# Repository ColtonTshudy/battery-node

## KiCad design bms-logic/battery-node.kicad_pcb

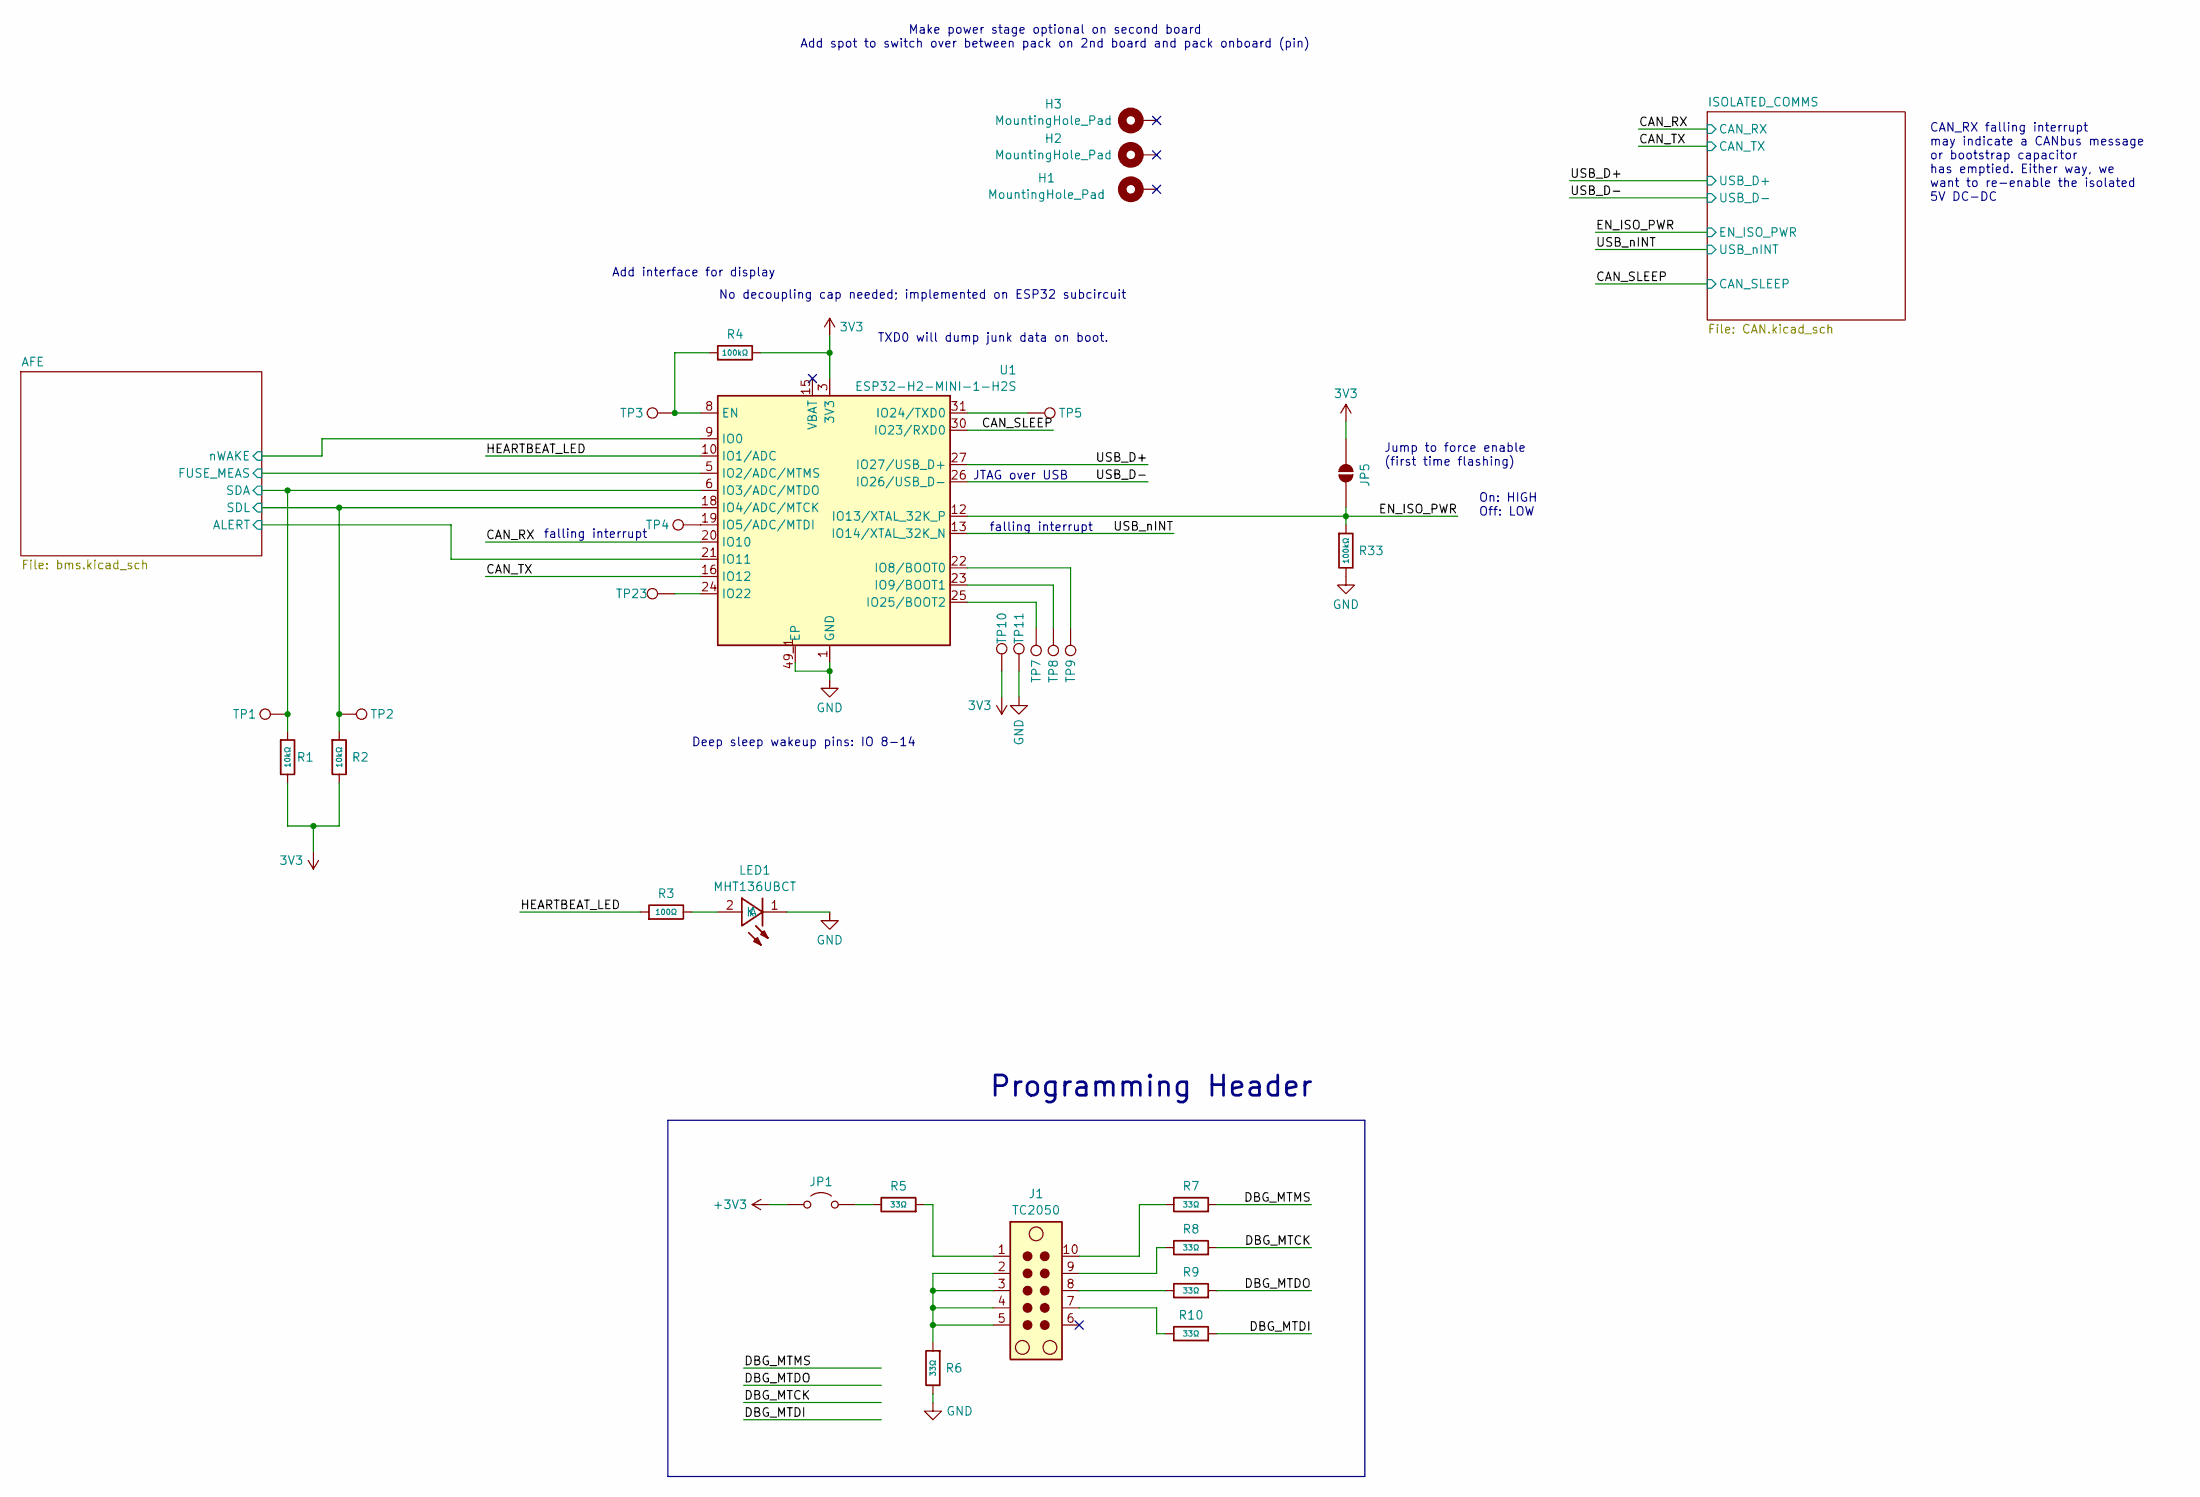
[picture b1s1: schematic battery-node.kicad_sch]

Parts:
H1, H2, H3: MountingHole_Pad; MountingHole_2.2mm_M2_DIN965_Pad_TopBottom
J1: TC2050; Tag-Connect_TC2050-IDC-NL_2x05_P1.27mm_Vertical
JP1: Jumper_2_Open; SolderJumper-2_P1.3mm_Open_RoundedPad1.0x1.5mm
JP5: SolderJumper_2_Open; SolderJumper-2_P1.3mm_Open_RoundedPad1.0x1.5mm
LED1: MHT136UBCT; Manufacturer Part MHT136UBCT; LCSC C401112
R1, R2: 10kΩ; R_0402; Overload Voltage (Max) 50V; Tolerance ±1%; Part 0402WGF1002TCE; LCSC C25744
R3: 100Ω; R_0402; Overload Voltage (Max) 50V; Tolerance ±1%; Part 0402WGF1000TCE; LCSC C25076
R4, R33: 100kΩ; R_0402; Overload Voltage (Max) 50V; Tolerance ±1%; Part 0402WGF1003TCE; LCSC C25741
R5, R6, R7, R8, R9, R10: 33Ω; R_0402; Overload Voltage (Max) 50V; Tolerance ±1%; Part 0402WGF330JTCE; LCSC C25105
TP1, TP2, TP3, TP4, TP5, TP10, TP11, TP23: IO25; TestPoint_Pad_D1.0mm
TP7, TP8, TP9: IO9; TestPoint_Pad_D1.0mm
U1: ESP32-H2-MINI-1-H2S; MODULE_ESP32-H2-MINI-1-H2; Part ESP32-H2-MINI-1-H2S

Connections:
3V3: JP5.2 (B), R1.2, R2.2, R4.2, TP10.1 (1_1), U1.3 (3V3); also elsewhere on the board
/AFE/ALERT: U1.21 (IO11); also elsewhere on the board
/AFE/FUSE_MEAS: U1.5 (IO2/ADC/MTMS)
/AFE/SDA: R1.1, TP1.1 (1_1), U1.6 (IO3/ADC/MTDO); also elsewhere on the board
/AFE/SDL: R2.1, TP2.1 (1_1), U1.18 (IO4/ADC/MTCK); also elsewhere on the board
/AFE/nWAKE: U1.9 (IO0); also elsewhere on the board
/CAN_RX: U1.20 (IO10); also elsewhere on the board
/CAN_SLEEP: U1.30 (IO23/RXD0); also elsewhere on the board
/CAN_TX: U1.16 (IO12); also elsewhere on the board
/EN_ISO_PWR: JP5.1 (A), R33.1, U1.12 (IO13/XTAL_32K_P); also elsewhere on the board
/HEARTBEAT_LED: R3.1, U1.10 (IO1/ADC)
/USB_D+: U1.27 (IO27/USB_D+); also elsewhere on the board
/USB_D-: U1.26 (IO26/USB_D-); also elsewhere on the board
/USB_nINT: U1.13 (IO14/XTAL_32K_N); also elsewhere on the board
GND: LED1.1 (K), R6.2, R33.2, TP11.1 (1_1), U1.1 (GND), U1.2 (GND), U1.11 (GND), U1.14 (GND), U1.36 (GND), U1.37 (GND), U1.38 (GND), U1.39 (GND), U1.40 (GND), U1.41 (GND), U1.42 (GND), U1.43 (GND), U1.44 (GND), U1.45 (GND), U1.46 (GND), U1.47 (GND), U1.48 (GND), U1.49_1 (EP), U1.49_2 (EP), U1.49_3 (EP), U1.49_4 (EP), U1.49_5 (EP), U1.49_6 (EP), U1.49_7 (EP), U1.49_8 (EP), U1.49_9 (EP), U1.50 (GND), U1.51 (GND), U1.52 (GND), U1.53 (GND), U1.54 (EP), U1.55 (EP), U1.56 (EP), U1.57 (EP), U1.58 (EP), U1.59 (EP), U1.60 (EP), U1.61 (EP), U1.62 (EP), U1.63 (EP), U1.64 (EP), U1.65 (EP); also elsewhere on the board
unnamed: J1.1, R5.1
unnamed: J1.2, J1.3, J1.4, J1.5, R6.1
unnamed: J1.7, R10.2
unnamed: J1.8, R9.2
unnamed: J1.9, R8.2
unnamed: J1.10, R7.2
unnamed: JP1.2 (B), R5.2
unnamed: LED1.2 (A), R3.2
unnamed: R4.1, TP3.1 (1_1), U1.8 (EN)
unnamed: TP4.1 (1_1), U1.19 (IO5/ADC/MTDI)
unnamed: TP9.1 (1_1), U1.22 (IO8/BOOT0)
unnamed: TP8.1 (1_1), U1.23 (IO9/BOOT1)
unnamed: TP23.1 (1_1), U1.24 (IO22)
unnamed: TP5.1 (1_1), U1.31 (IO24/TXD0)
unnamed: TP7.1 (1_1), U1.25 (IO25/BOOT2)

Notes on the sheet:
Jump to force enable (first time flashing)
On: HIGH Off: LOW
No decoupling cap needed; implemented on ESP32 subcircuit
CAN_RX falling interrupt may indicate a CANbus message or bootstrap capacitor has emptied. Either way, we want to re-enable the isolated 5V DC-DC
Make power stage optional on second board Add spot to switch over between pack on 2nd board and pack onboard (pin)
Deep sleep wakeup pins: IO 8-14
JTAG over USB
Add interface for display
Programming Header
falling interrupt
TXD0 will dump junk data on boot.

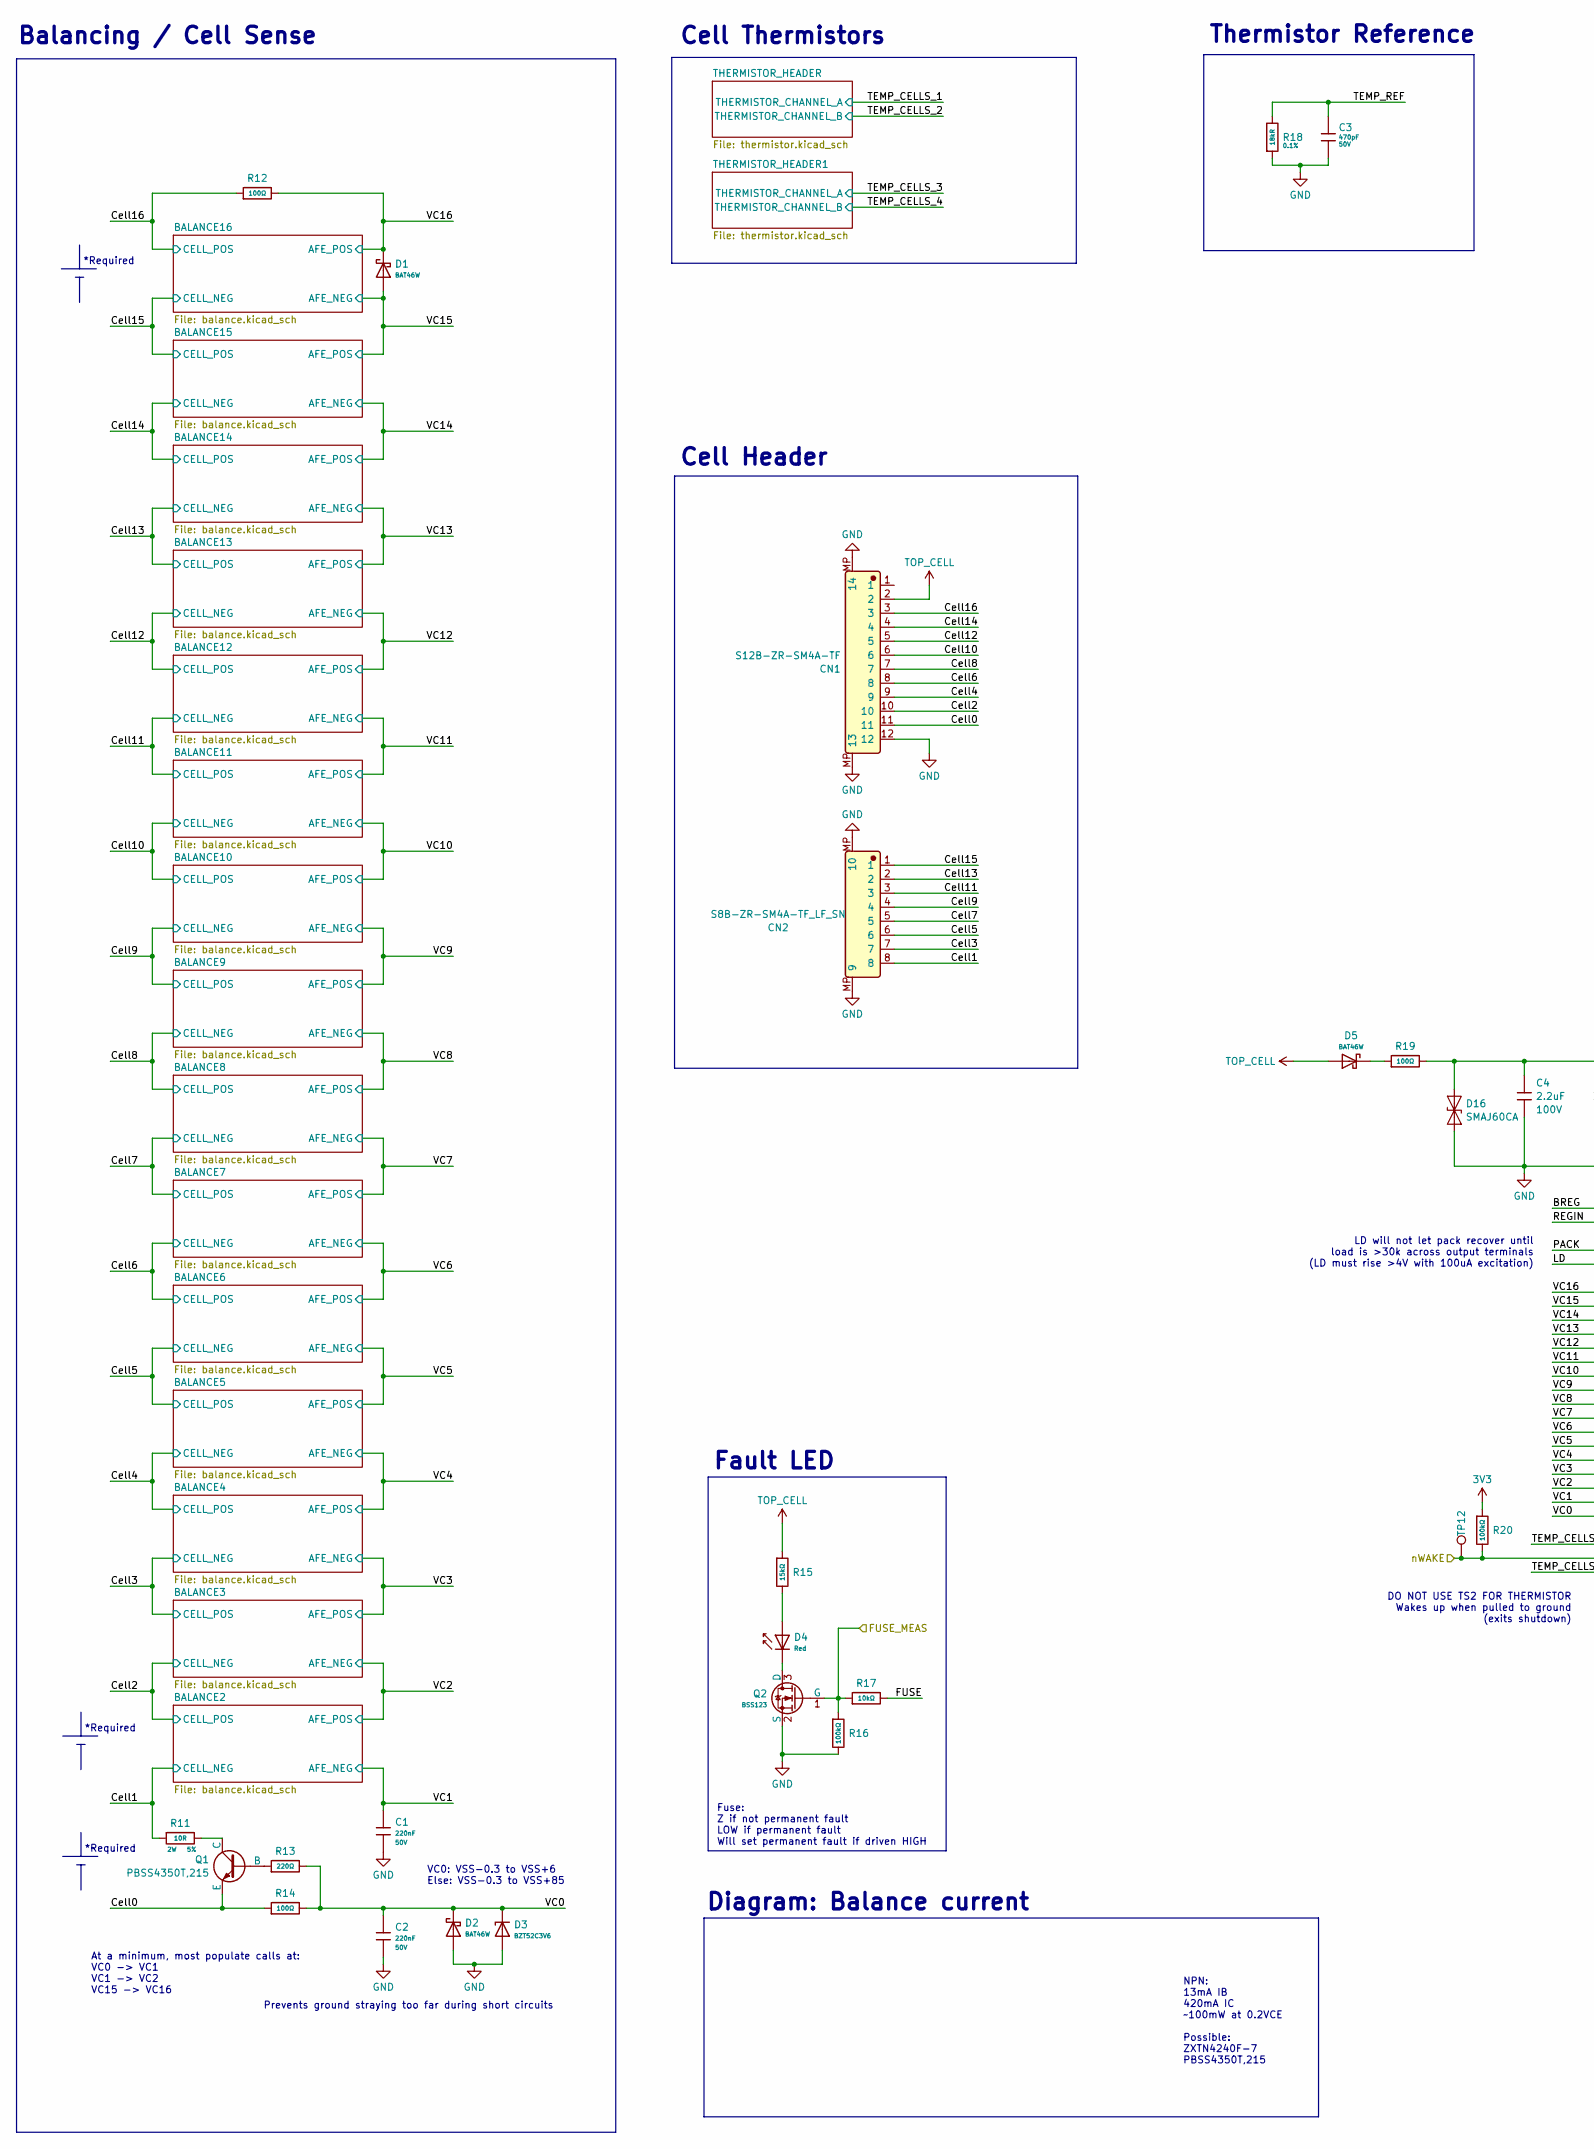
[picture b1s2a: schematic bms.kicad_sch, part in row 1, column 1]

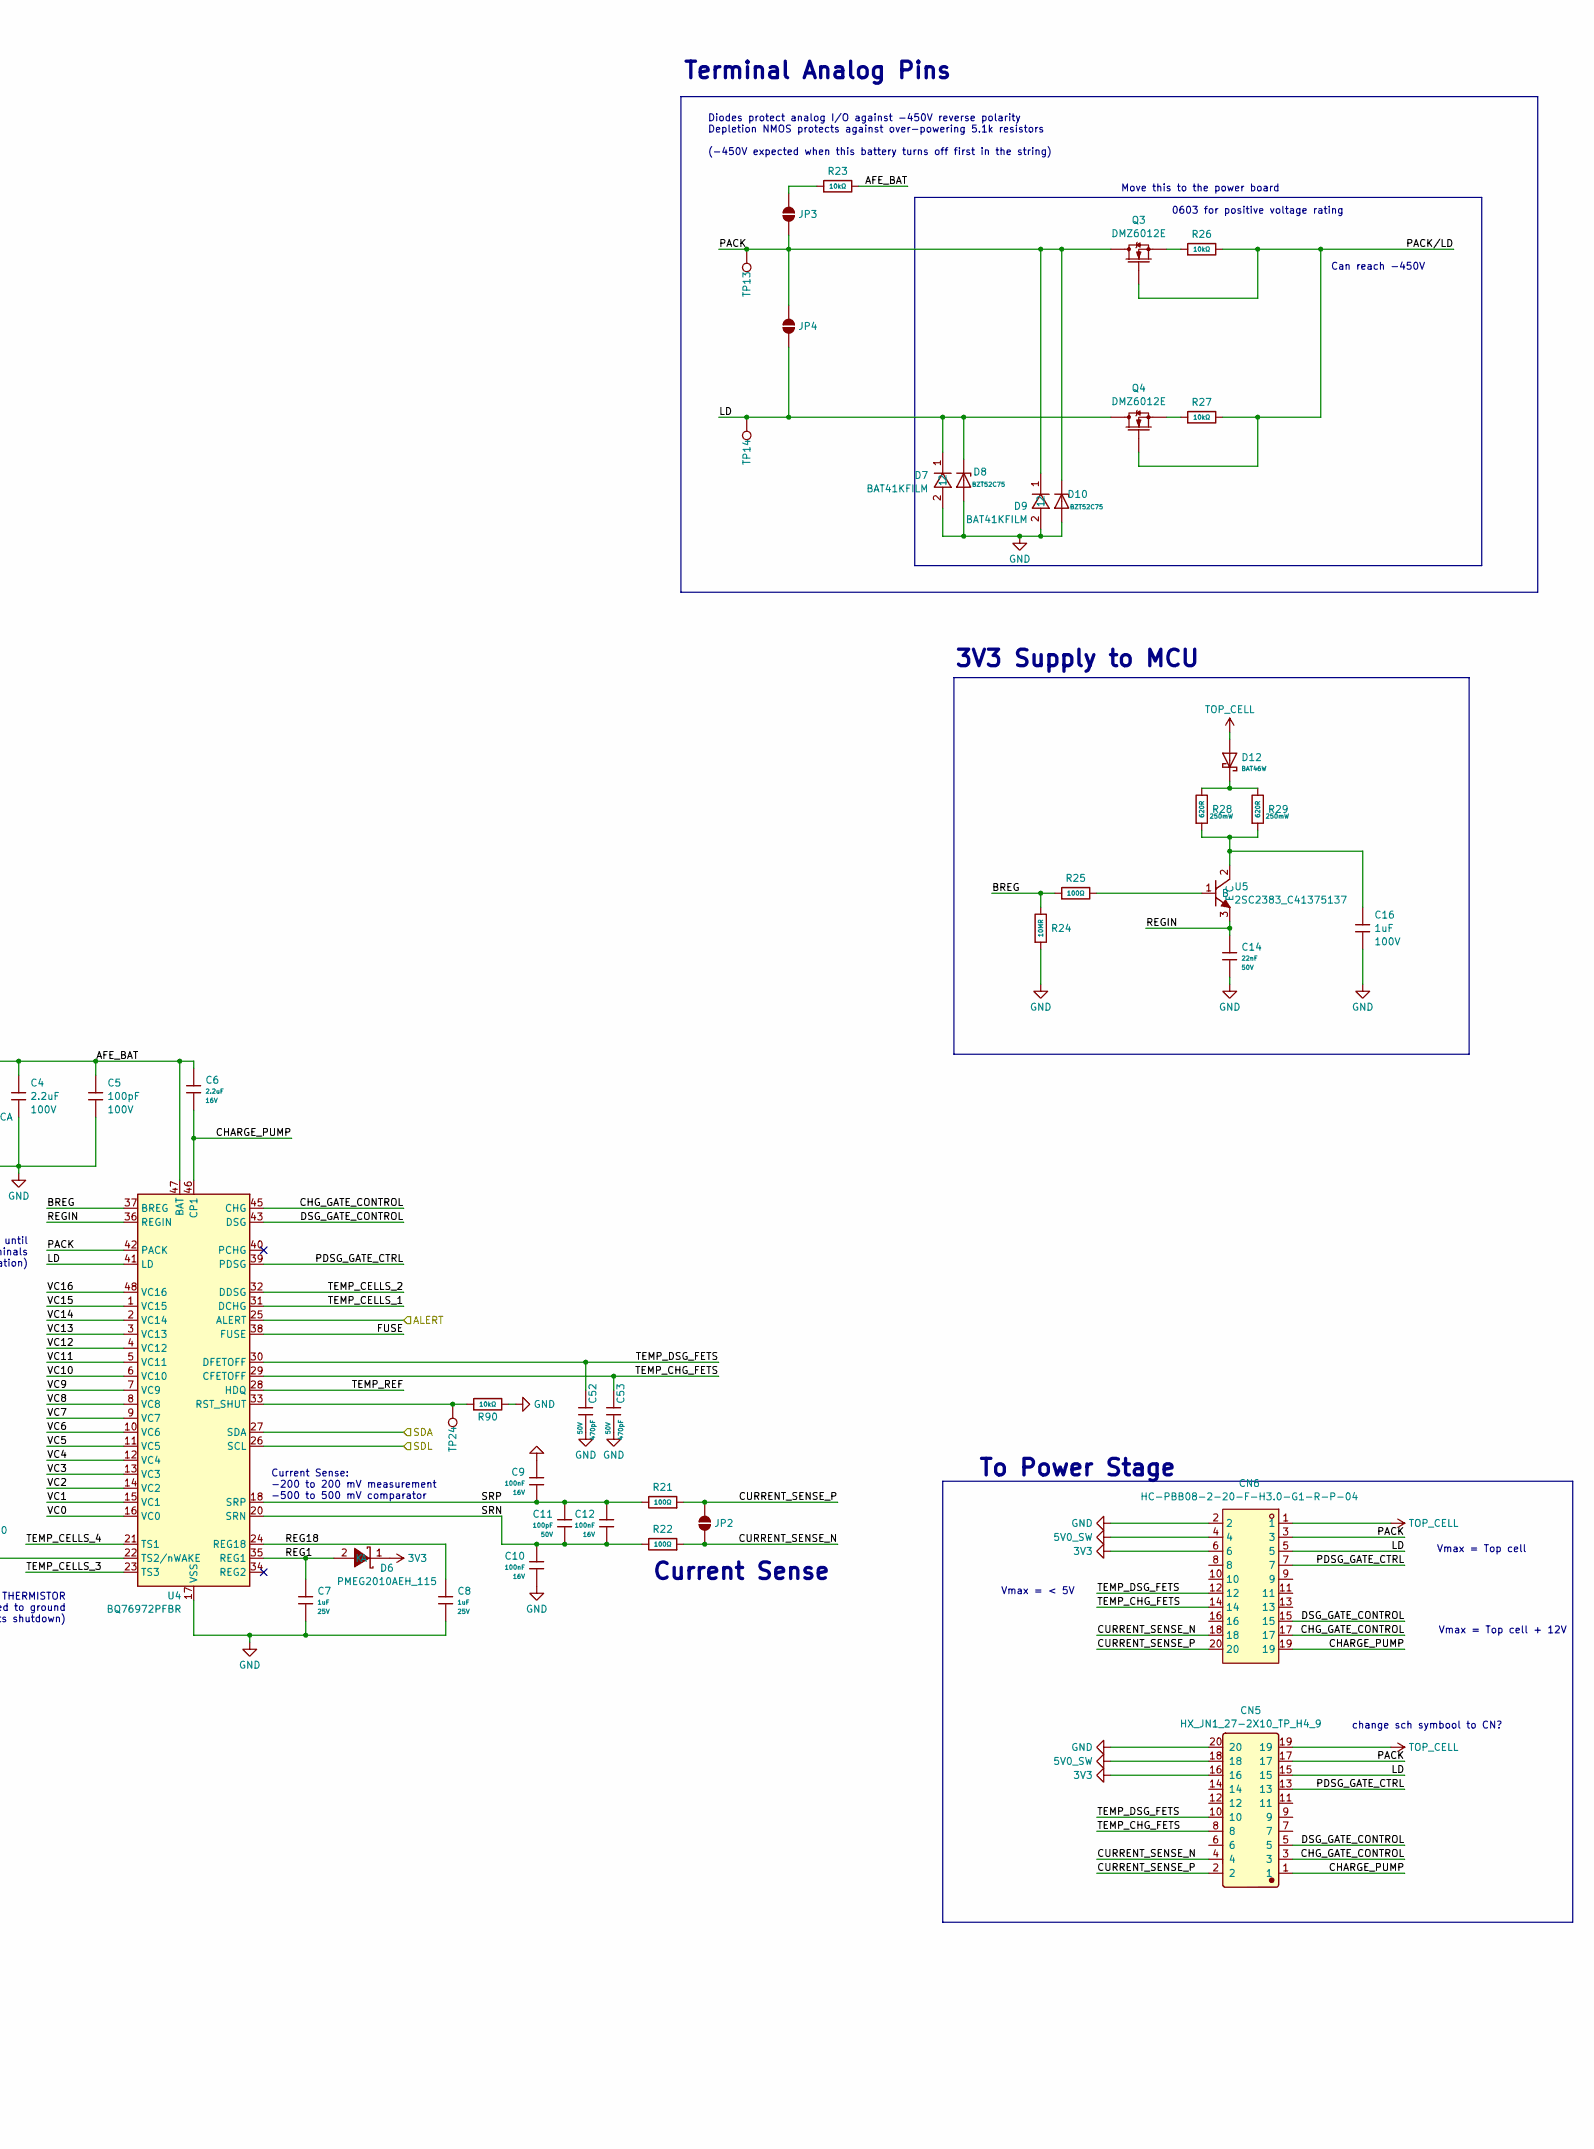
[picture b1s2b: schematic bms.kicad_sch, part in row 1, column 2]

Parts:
C1, C2: 220nF; C_0805; Voltage Rated 50V; Tolerance ±10%; Part CL21B224KBFNNNE; LCSC C5378
C3, C52, C53: 470pF; C_0402; Voltage Rated 50V; Tolerance ±10%; Part 0402B471K500NT; LCSC C1537
C4: 2.2uF; C_1206; Tolerance 10%; Voltage 100V; Part CC1206KKX7R0BB225
C5: 100pF; C_0603; Tolerance 5%; Voltage 100V; Part CC0603JRNPO0BN101
C6: 2.2uF; C_0603; Voltage Rated 16V; Tolerance ±10%; Part CL10A225KO8NNNC; LCSC C23630
C7, C8: 1uF; C_0402; Voltage Rated 25V; Tolerance ±10%; Part CL05A105KA5NQNC; LCSC C52923
C9, C10, C12: 100nF; C_0402; Voltage Rated 16V; Tolerance ±10%; Part CL05B104KO5NNNC; LCSC C1525
C11: 100pF; C_0402; Voltage Rated 50V; Tolerance ±5%; Part 0402CG101J500NT; LCSC C1546
C14: 22nF; C_0402; Voltage Rated 50V; Tolerance ±10%; Part 0402B223K500NT; LCSC C1532
C16: 1uF; C_0805; Tolerance 10%; Voltage 100V; Part CC0805KKX7R0BB105
CN1: S12B-ZR-SM4A-TF; JST_ZH_S12B-ZR-SM4A-TF_1x12-1MP_P1.50mm_Horizontal; Manufacturer Part S12B-ZR-SM4A-TF; LCSC C20089235
CN2: S8B-ZR-SM4A-TF_LF_SN; JST_ZH_S8B-ZR-SM4A-TF_1x08-1MP_P1.50mm_Horizontal; Manufacturer Part S8B-ZR-SM4A-TF(LF)(SN); LCSC C471474
CN5: HX_JN1_27-2X10_TP_H4_9; Manufacturer Part HX JN1.27-2x10 TP H4.9; LCSC C42455947
CN6: HC-PBB08-2-20-F-H3.0-G1-R-P-04; CONN-SMD_20P-P0.80_HC-PBB08-2-20-F-H4.0-G1-R-P-04; MPN HC-PBB08-2-20-F-H3.0-G1-R-P-04; LCSC Part C41421148
D1, D2, D5, D12: BAT46W; D_SOD-123; Forward Voltage (Vf@If) 450mV@10mA; Reverse Voltage (Vr) 100V; Part BAT46W; LCSC C7420332
D3: BZT52C3V6; D_SOD-123; Part BZT52C3V6; LCSC C19077397
D4: Red; D_0603; Part KT-0603R; LCSC C2286
D6: PMEG2010AEH_115; D_SOD-123FL; Manufacturer Part PMEG2010AEH,115; LCSC C110921
D7, D9: BAT41KFILM; D_SOD-523; Manufacturer Part BAT41KFILM; LCSC C73150
D8, D10: BZT52C75; D_SOD-123; Part BZT52C75; LCSC C22375297
D16: SMAJ60CA; D_SMA
JP2, JP3, JP4: SolderJumper_2_Open; SolderJumper-2_P1.3mm_Open_RoundedPad1.0x1.5mm
Q1: PBSS4350T,215; SOT-23; Part PBSS4350T,215
Q2: BSS123; Q_SOT-23; Part BSS123; LCSC C7420338
Q3, Q4: DMZ6012E; TSOT-23; Part DMZ6012E
R11: 10R; R_2512_6332Metric; Tolerance 5%; Part FRP2512J100 TS
R12, R14, R21, R22, R25: 100Ω; R_0402; Overload Voltage (Max) 50V; Tolerance ±1%; Part 0402WGF1000TCE; LCSC C25076
R13: 220Ω; R_0402; Tolerance ±1%; Overload Voltage (Max) 50V; Part 0402WGF2200TCE; LCSC C25091
R15: 15kΩ; R_0603; Overload Voltage (Max) 75V; Tolerance ±1%; Part 0603WAF1502T5E; LCSC C22809
R16, R20: 100kΩ; R_0402; Overload Voltage (Max) 50V; Tolerance ±1%; Part 0402WGF1003TCE; LCSC C25741
R17, R90: 10kΩ; R_0402; Overload Voltage (Max) 50V; Tolerance ±1%; Part 0402WGF1002TCE; LCSC C25744
R18: 18kR; R_0402; Tolerance 0.1%; Part RT0402BRD0718KL
R19: 100Ω; R_0603; Overload Voltage (Max) 75V; Tolerance ±1%; Part 0603WAF1000T5E; LCSC C22775
R23, R26, R27: 10kΩ; R_0603; Overload Voltage (Max) 75V; Tolerance ±1%; Part 0603WAF1002T5E; LCSC C25804
R24: 10MR; R_0402; Tolerance 5%; Part RC0402JR-0710ML
R28, R29: 620R; R_1206; Tolerance 1%; Part 1206W4F6200T5E
TP12, TP13, TP14, TP24: IO8; TestPoint_Pad_D1.0mm
U4: BQ76972PFBR; BQ76972
U5: 2SC2383_C41375137; SOT-89-3; Manufacturer Part 2SC2383; LCSC C41375137

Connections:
3V3: CN5.16, CN6.6, D6.1 (K), R20.1; also elsewhere on the board
5V0_SW: CN5.18, CN6.4; also elsewhere on the board
/AFE/AFE_BAT: C4.1, C5.1, C6.1, D16.2 (A2), R19.2, R23.2, U4.47 (BAT)
/AFE/ALERT: U4.25 (ALERT); also elsewhere on the board
/AFE/BREG: R24.1, R25.1, U4.37 (BREG)
/AFE/CHARGE_PUMP: C6.2, CN5.1, CN6.19, U4.46 (CP1)
/AFE/CHG_GATE_CONTROL: CN5.3, CN6.17, U4.45 (CHG)
/AFE/CURRENT_SENSE_N: CN5.4, CN6.18, JP2.1 (A), R22.1
/AFE/CURRENT_SENSE_P: CN5.2, CN6.20, JP2.2 (B), R21.1
/AFE/Cell0: CN1.11, Q1.2 (E), R14.1
/AFE/Cell1: CN2.8, R11.2; also elsewhere on the board
/AFE/Cell2: CN1.10; also elsewhere on the board
/AFE/Cell3: CN2.7; also elsewhere on the board
/AFE/Cell4: CN1.9; also elsewhere on the board
/AFE/Cell5: CN2.6; also elsewhere on the board
/AFE/Cell6: CN1.8; also elsewhere on the board
/AFE/Cell7: CN2.5; also elsewhere on the board
/AFE/Cell8: CN1.7; also elsewhere on the board
/AFE/Cell9: CN2.4; also elsewhere on the board
/AFE/Cell10: CN1.6; also elsewhere on the board
/AFE/Cell11: CN2.3; also elsewhere on the board
/AFE/Cell12: CN1.5; also elsewhere on the board
/AFE/Cell13: CN2.2; also elsewhere on the board
/AFE/Cell14: CN1.4; also elsewhere on the board
/AFE/Cell15: CN2.1; also elsewhere on the board
/AFE/Cell16: CN1.3, R12.1; also elsewhere on the board
/AFE/DSG_GATE_CONTROL: CN5.5, CN6.15, U4.43 (DSG)
/AFE/FUSE: R17.2, U4.38 (FUSE)
/AFE/LD: CN5.15, CN6.5, D7.1, D8.1, JP4.1 (A), Q4.3 (D), TP14.1 (1_1), U4.41 (LD)
/AFE/PACK: CN5.17, CN6.3, D9.1, D10.1, JP3.1 (A), JP4.2 (B), Q3.3 (D), TP13.1 (1_1), U4.42 (PACK)
/AFE/PDSG_GATE_CTRL: CN5.13, CN6.7, U4.39 (PDSG)
/AFE/REG1: C7.1, D6.2 (A), U4.35 (REG1)
/AFE/REG18: C8.1, U4.24 (REG18)
/AFE/REGIN: C14.1, U4.36 (REGIN), U5.3 (E)
/AFE/SDA: U4.27 (SDA); also elsewhere on the board
/AFE/SDL: U4.26 (SCL); also elsewhere on the board
/AFE/SRN: C10.1, C11.2, C12.2, R22.2, U4.20 (SRN)
/AFE/SRP: C9.2, C11.1, C12.1, R21.2, U4.18 (SRP)
/AFE/TEMP_CELLS_1: U4.31 (DCHG); also elsewhere on the board
/AFE/TEMP_CELLS_2: U4.32 (DDSG); also elsewhere on the board
/AFE/TEMP_CELLS_3: U4.23 (TS3); also elsewhere on the board
/AFE/TEMP_CELLS_4: U4.21 (TS1); also elsewhere on the board
/AFE/TEMP_CHG_FETS: C53.1, CN5.8, CN6.14, U4.29 (CFETOFF)
/AFE/TEMP_DSG_FETS: C52.1, CN5.10, CN6.12, U4.30 (DFETOFF)
/AFE/TEMP_REF: C3.1, R18.1, U4.28 (HDQ)
/AFE/VC0: C2.1, D2.1, D3.1, R13.2, R14.2, U4.16 (VC0)
/AFE/VC1: C1.1, U4.15 (VC1); also elsewhere on the board
/AFE/VC2: U4.14 (VC2); also elsewhere on the board
/AFE/VC3: U4.13 (VC3); also elsewhere on the board
/AFE/VC4: U4.12 (VC4); also elsewhere on the board
/AFE/VC5: U4.11 (VC5); also elsewhere on the board
/AFE/VC6: U4.10 (VC6); also elsewhere on the board
/AFE/VC7: U4.9 (VC7); also elsewhere on the board
/AFE/VC8: U4.8 (VC8); also elsewhere on the board
/AFE/VC9: U4.7 (VC9); also elsewhere on the board
/AFE/VC10: U4.6 (VC10); also elsewhere on the board
/AFE/VC11: U4.5 (VC11); also elsewhere on the board
/AFE/VC12: U4.4 (VC12); also elsewhere on the board
/AFE/VC13: U4.3 (VC13); also elsewhere on the board
/AFE/VC14: U4.2 (VC14); also elsewhere on the board
/AFE/VC15: D1.2, U4.1 (VC15); also elsewhere on the board
/AFE/VC16: D1.1, R12.2, U4.48 (VC16); also elsewhere on the board
/AFE/nWAKE: R20.2, TP12.1 (1_1), U4.22 (TS2/nWAKE); also elsewhere on the board
GND: C1.2, C2.2, C3.2, C4.2, C5.2, C7.2, C8.2, C9.1, C10.2, C14.2, C16.2, C52.2, C53.2, CN1.12, CN1.MP (14), CN2.MP (10), CN5.20, CN6.2, D2.2, D3.2, D7.2, D8.2, D9.2, D10.2, D16.1 (A1), Q2.2 (S), R16.2, R18.2, R24.2, R90.2, U4.17 (VSS); also elsewhere on the board
unnamed: D4.1, Q2.3 (D)
unnamed: D4.2, R15.2
unnamed: D5.1, R19.1
unnamed: D12.1, R28.1, R29.1
unnamed: JP3.2 (B), R23.1
unnamed: Q1.1 (B), R13.1
unnamed: Q1.3 (C), R11.1
unnamed: Q2.1 (G), R16.1, R17.1
unnamed: Q3.1 (G), Q4.1 (G), R26.2, R27.2
unnamed: Q3.2 (S), R26.1
unnamed: Q4.2 (S), R27.1
unnamed: R90.1, TP24.1 (1_1), U4.33 (RST_SHUT)
unnamed: R25.2, U5.1 (B)
unnamed: C16.1, R28.2, R29.2, U5.2 (C)
TOP_CELL: CN1.2, CN5.19, CN6.1, D5.2, D12.2, R15.1; also elsewhere on the board

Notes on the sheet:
change sch symbool to CN?
Vmax = < 5V
At a minimum, most populate calls at: VC0 -> VC1 VC1 -> VC2 VC15 -> VC16
Can reach -450V
Cell Thermistors
*Required
Thermistor Reference
Cell Header
Diagram: Balance current
Move this to the power board
To Power Stage
LD will not let pack recover until load is >30k across output terminals (LD must rise >4V with 100uA excitation)
VC0: VSS-0.3 to VSS+6 Else: VSS-0.3 to VSS+85
Fuse: Z if not permanent fault LOW if permanent fault Will set permanent fault if driven HIGH
Vmax = Top cell + 12V
DO NOT USE TS2 FOR THERMISTOR Wakes up when pulled to ground (exits shutdown)
Prevents ground straying too far during short circuits
Fault LED
Vmax = Top cell
0603 for positive voltage rating
Current Sense
Diodes protect analog I/O against -450V reverse polarity Depletion NMOS protects against over-powering 5.1k resistors (-450V expected when this battery turns off first in the string)
NPN: 13mA IB 420mA IC ~100mW at 0.2VCE Possible: ZXTN4240F-7 PBSS4350T,215
Current Sense: -200 to 200 mV measurement -500 to 500 mV comparator
3V3 Supply to MCU
Terminal Analog Pins
Balancing / Cell Sense

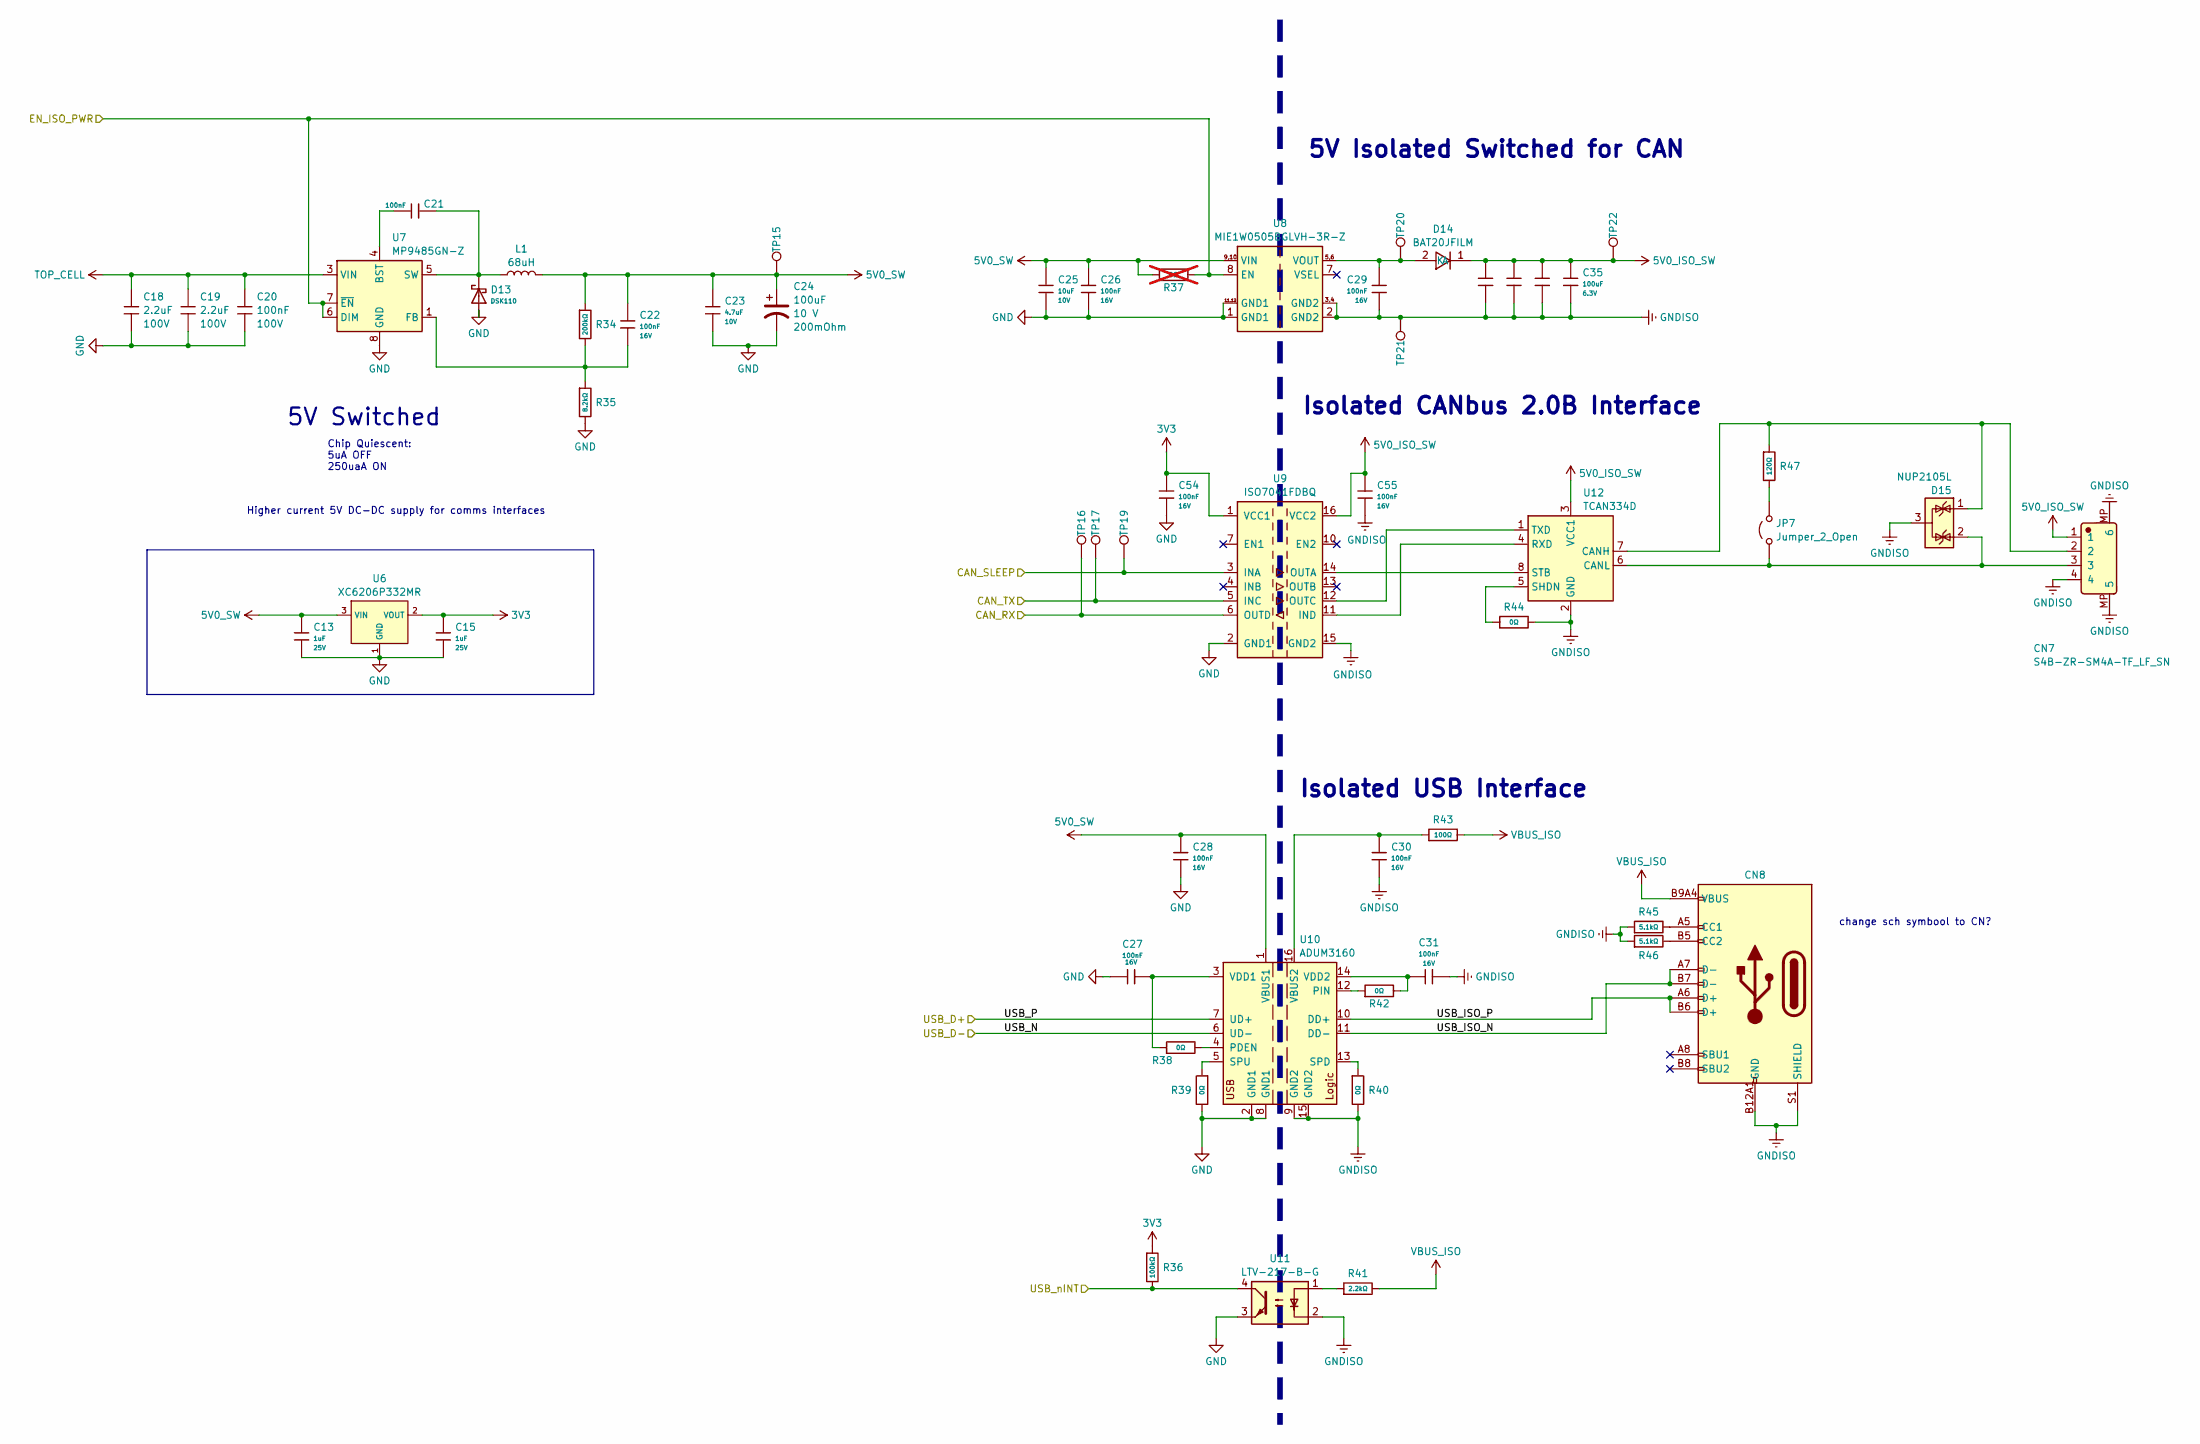
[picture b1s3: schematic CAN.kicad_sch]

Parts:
C13, C15: 1uF; C_0402; Voltage Rated 25V; Tolerance ±10%; Part CL05A105KA5NQNC; LCSC C52923
C18, C19: 2.2uF; C_1206; Tolerance 10%; Voltage 100V; Part CC1206KKX7R0BB225
C20: 100nF; C_0805; Tolerance 10%; Voltage 100V; Part CL21B104KCFNNNE
C21, C22, C26, C27, C28, C29, C30, C31, C54, C55: 100nF; C_0402; Voltage Rated 16V; Tolerance ±10%; Part CL05B104KO5NNNC; LCSC C1525
C23: 4.7uF; C_0402; Voltage Rated 10V; Tolerance ±20%; Part CL05A475MP5NRNC; LCSC C23733
C24: 100uF; CP_EIA-6032-20_AVX-F; Tolerance 10%; Voltage 10 V; Part TR3C107K010C0200
C25: 10uF; C_0603; Voltage Rated 10V; Tolerance ±10%; Part CL10A106KP8NNNC; LCSC C19702
C32, C33, C34, C35: 100uF; C_1206; Voltage Rated 6.3V; Tolerance ±20%; Part CL31A107MQHNNNE; LCSC C15008
CN7: S4B-ZR-SM4A-TF_LF_SN; JST_ZH_S4B-ZR-SM4A-TF_1x04-1MP_P1.50mm_Horizontal; Manufacturer Part S4B-ZR-SM4A-TF(LF)(SN); LCSC C485354
CN8: Connector, USB-TYPE-C-16P; TYPE-C-SMD_HX-TYPE-C-16PIN; LCSC C2927039
D13: DSK110; D_SOD-123FL; Part DSK110; LCSC C22466354
D14: BAT20JFILM; Manufacturer Part BAT20JFILM; LCSC C155590
D15: NUP2105L; SOT-23
JP7: Jumper_2_Open; SolderJumper-2_P1.3mm_Open_RoundedPad1.0x1.5mm
L1: 68uH; L_Changjiang_FTC404020S; Tolerance 20%; Part FNR4020S680MT
R34: 200kΩ; R_0402; Overload Voltage (Max) 50V; Tolerance ±1%; Part 0402WGF2003TCE; LCSC C25764
R35: 8.2kΩ; R_0402; Overload Voltage (Max) 50V; Tolerance ±1%; Part 0402WGF8201TCE; LCSC C25924
R36: 100kΩ; R_0402; Overload Voltage (Max) 50V; Tolerance ±1%; Part 0402WGF1003TCE; LCSC C25741
R37: 0Ω; R_0402; Overload Voltage (Max) 50V; Tolerance ±1%; Part 0402WGF0000TCE; LCSC C17168; not fitted
R38, R39, R40, R42, R44: 0Ω; R_0402; Overload Voltage (Max) 50V; Tolerance ±1%; Part 0402WGF0000TCE; LCSC C17168
R41: 2.2kΩ; R_0402; Overload Voltage (Max) 50V; Tolerance ±1%; Part 0402WGF2201TCE; LCSC C25879
R43: 100Ω; R_0402; Overload Voltage (Max) 50V; Tolerance ±1%; Part 0402WGF1000TCE; LCSC C25076
R45, R46: 5.1kΩ; R_0402; Overload Voltage (Max) 50V; Tolerance ±1%; Part 0402WGF5101TCE; LCSC C25905
R47: 120Ω; R_0402; Overload Voltage (Max) 50V; Tolerance ±1%; Part 0402WGF1200TCE; LCSC C25079
TP15, TP16, TP17, TP19, TP20, TP21, TP22: IO8; TestPoint_Pad_D1.0mm
U6: XC6206P332MR; SOT-23-3_L2.9-W1.6-P1.90-LS2.8-BR; Output Voltage 3.3V; Dropout Voltage 680mV@(100mA); Part XC6206P332MR-G; LCSC C5446
U7: MP9485GN-Z
U8: MIE1W0505BGLVH-3R-Z
U9: ISO7041FDBQ; SOIC-16W_7.5x10.3mm_P1.27mm
U10: ADUM3160; SOIC-16W_7.5x10.3mm_P1.27mm
U11: LTV-217-B-G; SOP-4_4.4x2.6mm_P1.27mm; Part LTV-217-B-G; LCSC C115450
U12: TCAN334D

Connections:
3V3: C15.1, C54.1, R36.1, U6.2 (VOUT), U9.1 (VCC1); also elsewhere on the board
5V0_ISO_SW: C32.1, C33.1, C34.1, C35.1, C55.1, CN7.1, D14.1 (K), TP22.1 (1_1), U9.16 (VCC2), U12.3 (VCC1)
5V0_SW: C13.1, C22.2, C23.1, C24.1, C25.1, C26.1, C28.1, L1.2, R34.1, R37.1, TP15.1 (1_1), U6.3 (VIN), U8.9,10 (VIN), U10.1 (VBUS1); also elsewhere on the board
/CAN_RX: TP16.1 (1_1), U9.6 (OUTD); also elsewhere on the board
/CAN_SLEEP: TP19.1 (1_1), U9.3 (INA); also elsewhere on the board
/CAN_TX: TP17.1 (1_1), U9.5 (INC); also elsewhere on the board
/EN_ISO_PWR: R37.2, U7.6 (DIM), U7.7 (~EN), U8.8 (EN); also elsewhere on the board
/ISOLATED_COMMS/USB_ISO_N: CN8.A7 (D-), CN8.B7 (D-), U10.11 (DD-)
/ISOLATED_COMMS/USB_ISO_P: CN8.A6 (D+), CN8.B6 (D+), U10.10 (DD+)
/USB_D+: U10.7 (UD+); also elsewhere on the board
/USB_D-: U10.6 (UD-); also elsewhere on the board
/USB_nINT: R36.2, U11.4; also elsewhere on the board
GND: C13.2, C15.2, C18.2, C19.2, C20.2, C23.2, C24.2, C25.2, C26.2, C27.2, C28.2, C54.2, D13.2, R35.2, R39.2, U6.1 (GND), U7.8 (GND), U7.9 (GND), U8.1 (GND1), U8.11,12 (GND1), U9.2 (GND1), U9.8 (GND1), U10.2 (GND1), U10.8 (GND1), U11.3; also elsewhere on the board
GNDISO: C29.2, C30.2, C31.1, C32.2, C33.2, C34.2, C35.2, C55.2, CN7.4, CN7.MP (6), CN8.A12B1 (GND), CN8.B12A1 (GND), CN8.S1 (SHIELD), D15.3 (A), R40.2, R44.2, R45.1, R46.1, TP21.1 (1_1), U8.2 (GND2), U8.3,4 (GND2), U9.9 (GND2), U9.15 (GND2), U10.9 (GND2), U10.15 (GND2), U11.2, U12.2 (GND)
unnamed: CN8.A5 (CC1), R45.2
unnamed: CN8.B5 (CC2), R46.2
unnamed: C29.1, D14.2 (A), TP20.1 (1_1), U8.5,6 (VOUT)
unnamed: CN7.3, D15.2 (K), JP7.1 (A), U12.6 (CANL)
unnamed: JP7.2 (B), R47.2
unnamed: R41.1, U11.1
unnamed: C21.2, U7.4 (BST)
unnamed: C22.1, R34.2, R35.1, U7.1 (FB)
unnamed: C21.1, D13.1, L1.1, U7.5 (SW)
unnamed: R38.2, U10.4 (PDEN)
unnamed: R42.1, U10.12 (PIN)
unnamed: R40.1, U10.13 (SPD)
unnamed: R39.1, U10.5 (SPU)
unnamed: C30.1, R43.1, U10.16 (VBUS2)
unnamed: C27.1, R38.1, U10.3 (VDD1)
unnamed: C31.2, R42.2, U10.14 (VDD2)
unnamed: CN7.2, D15.1 (K), R47.1, U12.7 (CANH)
unnamed: U9.11 (IND), U12.4 (RXD)
unnamed: R44.1, U12.5 (SHDN)
unnamed: U9.14 (OUTA), U12.8 (STB)
unnamed: U9.12 (OUTC), U12.1 (TXD)
TOP_CELL: C18.1, C19.1, C20.1, U7.3 (VIN); also elsewhere on the board
VBUS_ISO: CN8.A9B4 (VBUS), CN8.B9A4 (VBUS), R41.2, R43.2

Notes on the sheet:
5V Isolated Switched for CAN
Isolated USB Interface
5V Switched
change sch symbool to CN?
Isolated CANbus 2.0B Interface
Chip Quiescent: 5uA OFF 250uaA ON
Higher current 5V DC-DC supply for comms interfaces
